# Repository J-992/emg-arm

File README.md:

# EMG-Prosthetic-Arm
Prosthetic arm crit files

- need to fabricate custom pcb DONE
- need to design hand prototype 
- need to design finger/hand actuation mechanism

Code Reqs:
- class to import real time servo data
- class to process servo data (converting to either motor or LEDs)
- (Experimental): using AI to "assume" movements based on historical/logged data

Use cpp to receive and send info to arduino,
use python to process it?

- 3D cad (fingers, palm support, amputee compatibility)

Process:
- initial designs
- Design individual finger, figure out how to make it move
- 
=======
(STILL IN DEVELOPMENT)

loads of delay as chip design took multiple iterations
>>>>>>> 50d2780ce292e68660c6f66260bad24d6c35f479

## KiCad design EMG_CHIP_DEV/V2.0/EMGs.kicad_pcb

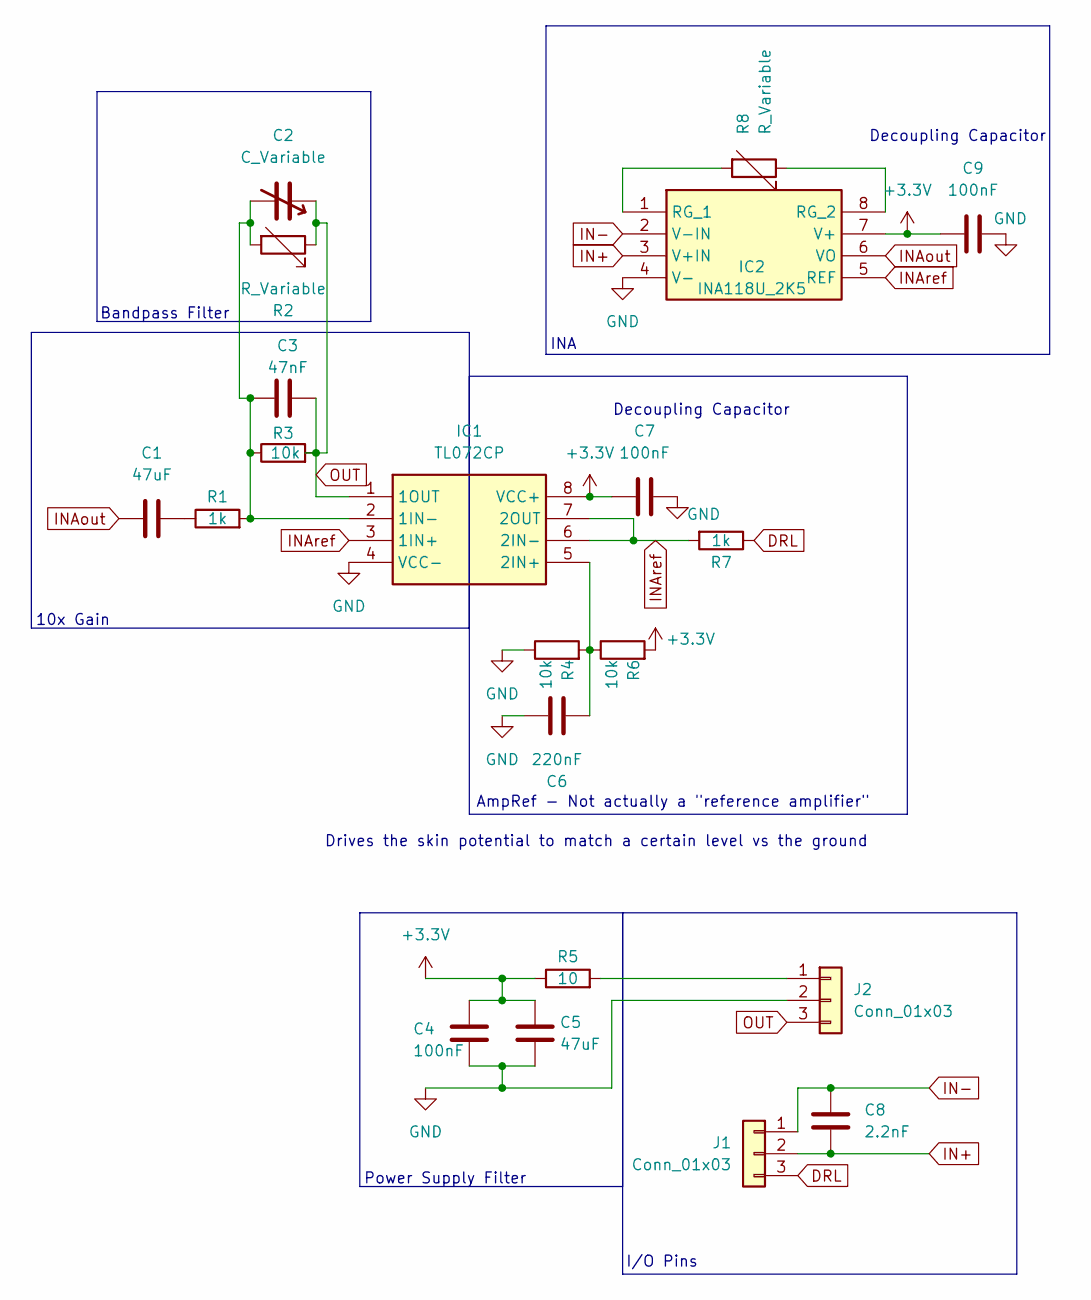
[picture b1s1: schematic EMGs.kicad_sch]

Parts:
C1, C5: 47uF; C_1206_3216Metric
C2: C_Variable; C_1206_3216Metric
C3: 47nF; C_1206_3216Metric
C4, C7, C9: 100nF; C_1206_3216Metric
C6: 220nF; C_1206_3216Metric
C8: 2.2nF; C_1206_3216Metric
IC1: TL072CP; DIP794W53P254L959H508Q8N; Mouser Part Number 595-TL072CP
IC2: INA118U_2K5; SOIC127P600X175-8N; Mouser Part Number 595-INA118U/2K5
J1, J2: Conn_01x03; PinHeader_1x03_P2.54mm_Vertical
R1, R7: 1k; R_0805_2012Metric
R2, R8: R_Variable; R_0805_2012Metric
R3, R4, R6: 10k; R_0805_2012Metric
R5: 10; R_0805_2012Metric

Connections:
+3.3V: C4.1, C5.1, C7.1, C9.1, IC1.8 (VCC+), IC2.7 (V+), R5.1, R6.2
DRL: J1.3, R7.1
GND: C4.2, C5.2, C6.2, C7.2, C9.2, IC1.4 (VCC-), IC2.4 (V-), J2.2, R4.1
IN+: C8.2, IC2.3 (V+IN), J1.2
IN-: C8.1, IC2.2 (V-IN), J1.1
INAout: C1.1, IC2.6 (VO)
INAref: IC1.3 (1IN+), IC1.6 (2IN-), IC1.7 (2OUT), IC2.5 (REF), R7.2
unnamed: C1.2, R1.1
unnamed: C2.2, C3.1, IC1.2 (1IN-), R1.2, R2.2, R3.1
unnamed: C6.1, IC1.5 (2IN+), R4.2, R6.1
unnamed: IC2.1 (RG_1), R8.2
unnamed: IC2.8 (RG_2), R8.1
unnamed: J2.1, R5.2
OUT: C2.1, C3.2, IC1.1 (1OUT), J2.3, R2.1, R3.2

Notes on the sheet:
10x Gain
AmpRef - Not actually a "reference amplifier"
INA
Power Supply Filter
Decoupling Capacitor
Bandpass Filter
I/O Pins
Drives the skin potential to match a certain level vs the ground

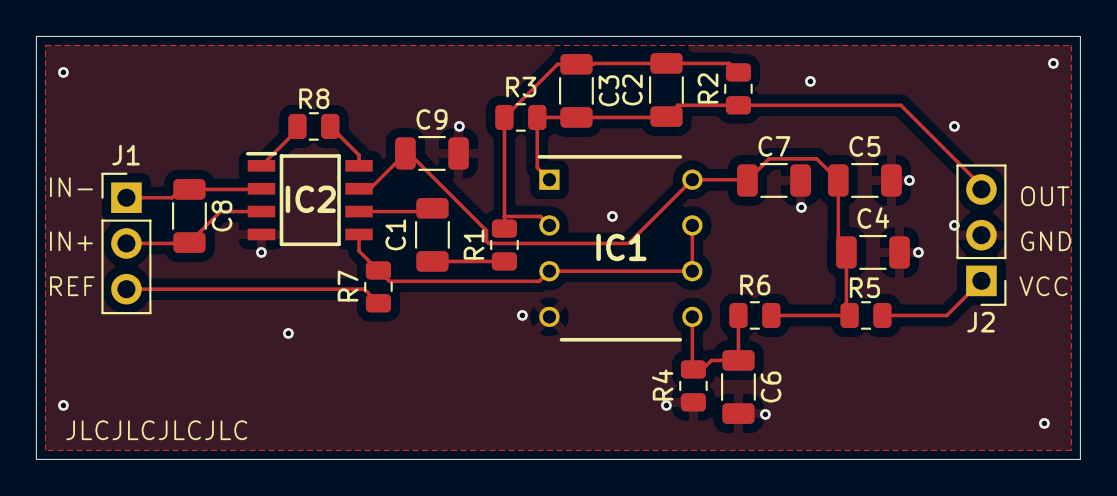
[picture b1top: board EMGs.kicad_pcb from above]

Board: 2 copper layers, 58.0 x 23.5 mm, 21 parts (0 on the bottom side), 14 nets.

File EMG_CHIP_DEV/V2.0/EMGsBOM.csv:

"Id";"Designator";"Footprint";"Quantity";"Designation";"Supplier and ref";
1;"IC1";"DIP794W53P254L959H508Q8N";1;"TL072CP";;;
2;"C5,C1";"C_1206_3216Metric";2;"47uF";;;
3;"C7,C4,C9";"C_1206_3216Metric";3;"100nF";;;
4;"C3";"C_1206_3216Metric";1;"47nF";;;
5;"R4,R6,R3";"R_0805_2012Metric";3;"10k";;;
6;"C2";"C_1206_3216Metric";1;"C_Variable";;;
7;"R2,R8";"R_0805_2012Metric";2;"R_Variable";;;
8;"J2,J1";"PinHeader_1x03_P2.54mm_Vertical";2;"Conn_01x03";;;
9;"R1,R7";"R_0805_2012Metric";2;"1k";;;
10;"C8";"C_1206_3216Metric";1;"2.2nF";;;
11;"R5";"R_0805_2012Metric";1;"10";;;
12;"C6";"C_1206_3216Metric";1;"220nF";;;
13;"IC2";"SOIC127P600X175-8N";1;"INA118U_2K5";;;

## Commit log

2023-07-13 Create config.py
    Main config files to code arduino with python
2023-07-13 Create emg_data.py
    Extracts data from emg sensors
2024-05-06 poop
2024-05-30 o
    o
2024-07-12 oo
    oo
